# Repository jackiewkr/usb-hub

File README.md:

# 5.25" drive bay USB hub

## Why?
My PC case lacks front IO, due to it being from the early 90s. As such, all the USB headers
are located at the back of the motherboard. The pin headers for front IO on my motherboard
are unused, so this project should rectify that.

## What?
The aim is to create a 4-port USB hub, able to be mounted within a 5.25" PC drive bay.
More (semi-)detailed specifications below:
- Have 4 downstream USB 2.0 high-speed capable ports
- Be powered by standard Molex connector (aka 4-pin peripheral power connectors)
- Include current sensing on a port-by-port basis (don't kill all ports if only one overcurrents)
- Need no configuration from the user (work automatically once connected)
- Not to kill my motherboard or power supply

## Current Status
- Schematic designed fully [done]
- Initial PCB layout designed [working]
- First boards manufactured & tested [not yet]
- Revised boards [not yet]
- Outer case designed & printed [not yet]

## Schematic Details
The design is based of the Microchip USB2504, a 4-port USB 2.0 hub controller IC. 
The schematic largely follows the design of the evaluation board schematic, with
changes to limit certain functionality (no LEDs, EVB uses ganged current sensing, etc.)

Note that this schematic uses the TPS2560 for current sensing. The OUT1, OUT2 pins
are mis-assigned in the KiCad library as Output instead of Power Output. Please ignore
any errors generated in the DRC due to this.

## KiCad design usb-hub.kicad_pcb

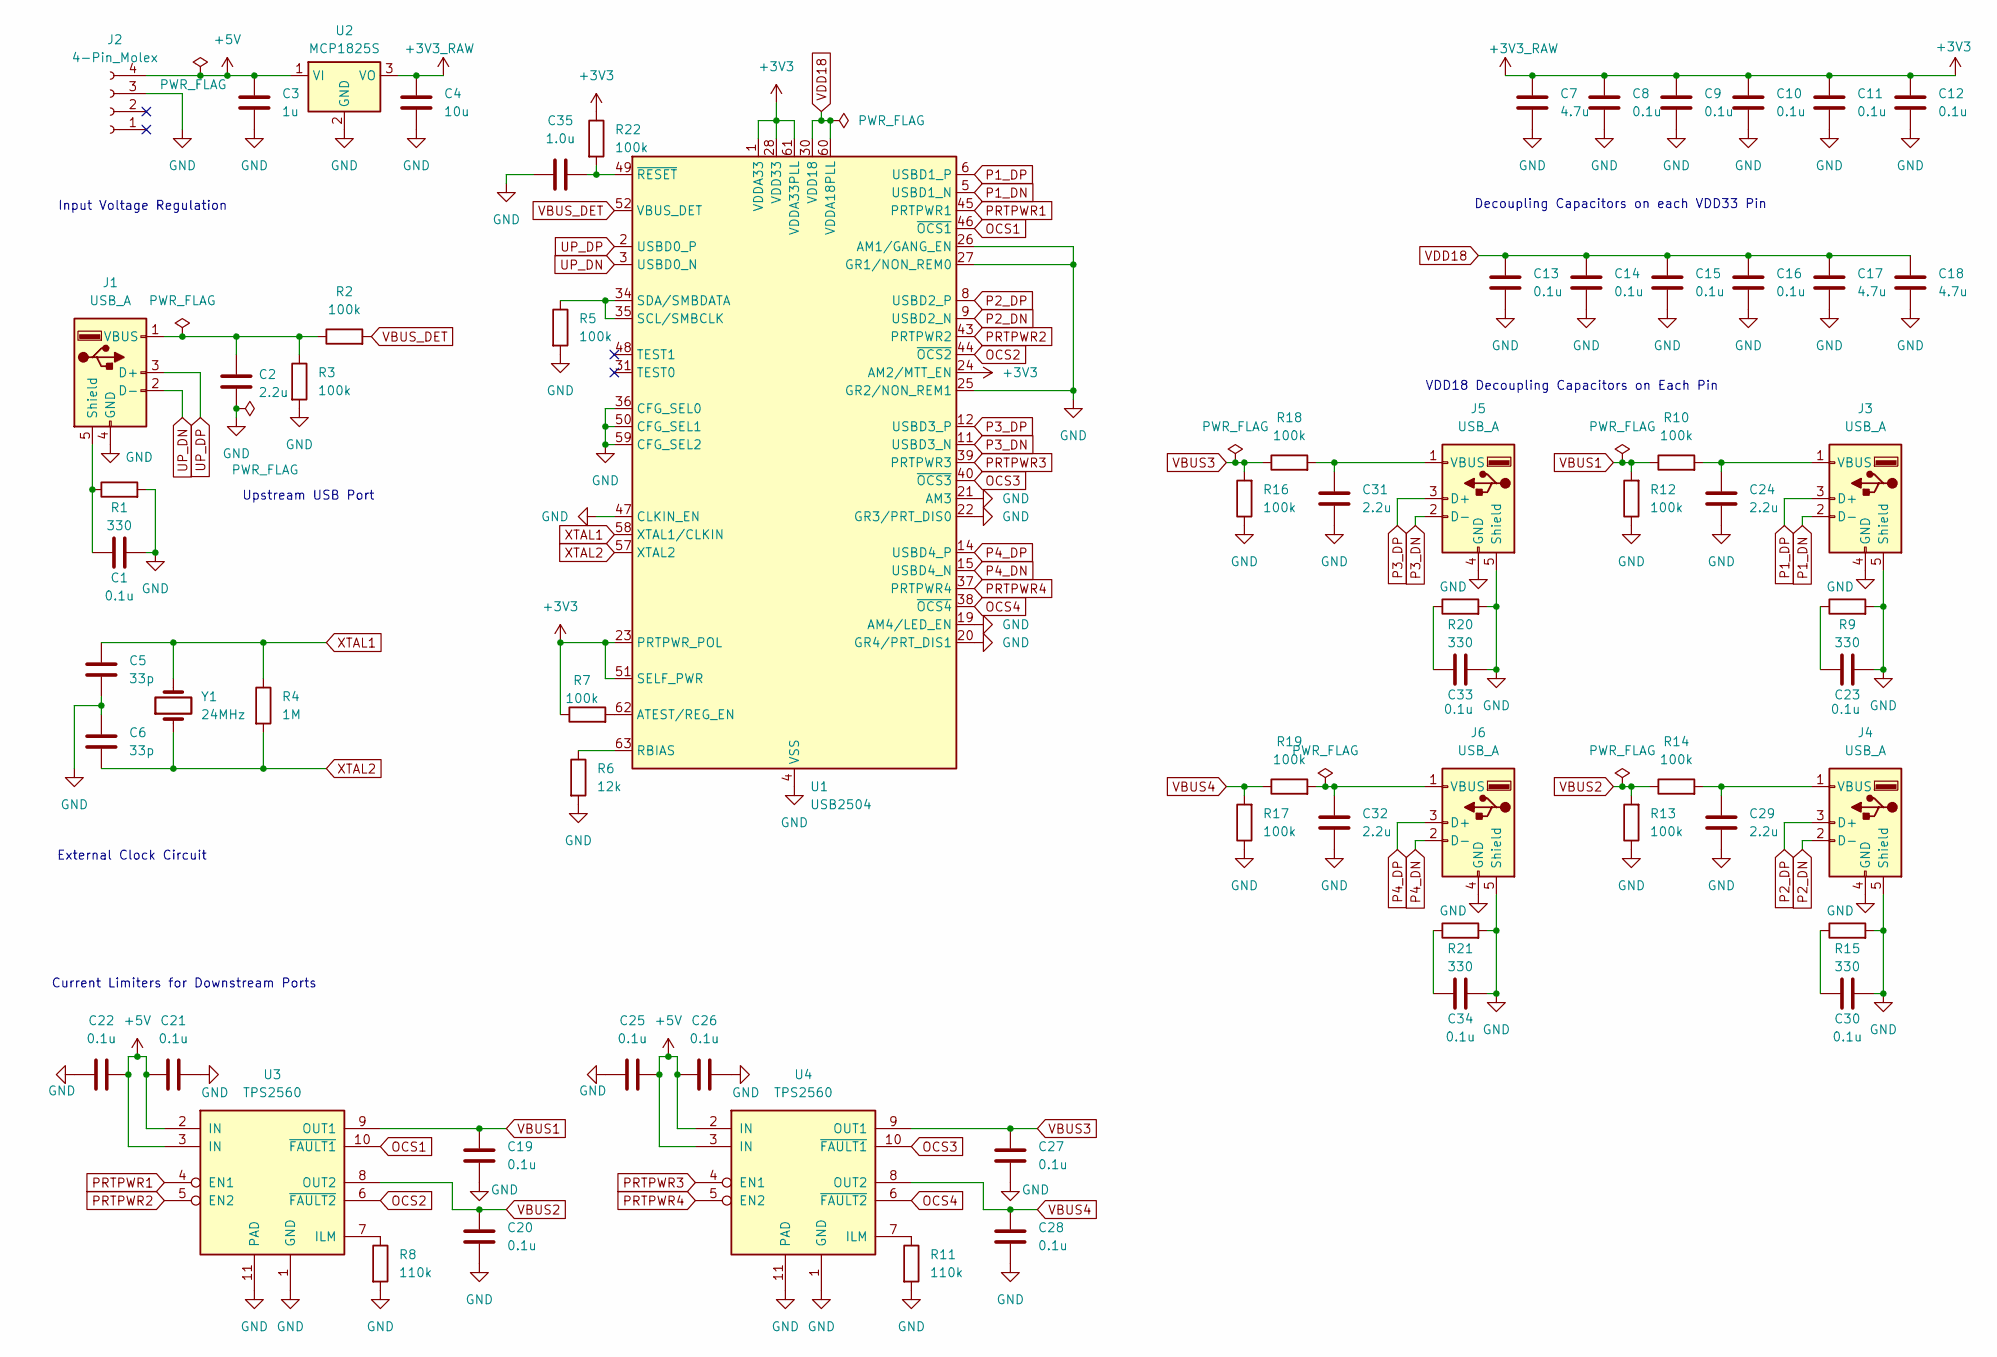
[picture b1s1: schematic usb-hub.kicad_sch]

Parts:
C1, C8, C9, C10, C11, C12, C13, C14, C15, C16, C19, C20, C21, C22, C23, C25, C26, C27, C28, C30, C33, C34: 0.1u; R_0805_2012Metric_Pad1.20x1.40mm_HandSolder
C2, C24, C29, C31, C32: 2.2u; R_0805_2012Metric_Pad1.20x1.40mm_HandSolder
C3: 1u; R_0805_2012Metric_Pad1.20x1.40mm_HandSolder
C4: 10u; R_0805_2012Metric_Pad1.20x1.40mm_HandSolder
C5, C6: 33p; R_0805_2012Metric_Pad1.20x1.40mm_HandSolder
C7, C17, C18: 4.7u; R_0805_2012Metric_Pad1.20x1.40mm_HandSolder
C35: 1.0u; R_0805_2012Metric_Pad1.20x1.40mm_HandSolder
J1, J3, J4, J5, J6: USB_A; USB_A_Receptacle_GCT_USB1046
J2: 4-Pin_Molex; SolderWire-1sqmm_1x04_P5.4mm_D1.4mm_OD2.7mm
R1, R9, R15, R20, R21: 330; R_0805_2012Metric_Pad1.20x1.40mm_HandSolder
R2, R3, R5, R7, R10, R12, R13, R14, R16, R17, R18, R19, R22: 100k; R_0805_2012Metric_Pad1.20x1.40mm_HandSolder
R4: 1M; R_0805_2012Metric_Pad1.20x1.40mm_HandSolder
R6: 12k; R_0805_2012Metric_Pad1.20x1.40mm_HandSolder
R8, R11: 110k; R_0805_2012Metric_Pad1.20x1.40mm_HandSolder
U1: USB2504; LQFP-64_10x10mm_P0.5mm
U2: MCP1825S; SOT-223
U3, U4: TPS2560; VSON-10-1EP_3x3mm_P0.5mm_EP1.65x2.4mm_ThermalVias
Y1: 24MHz; Crystal_SMD_2016-4Pin_2.0x1.6mm

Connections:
+3V3: C4.1, C7.1, C8.1, C9.1, C10.1, C11.1, C12.1, R7.1, R22.1, U1.1 (VDDA33), U1.7 (VDDA33), U1.13 (VDDA33), U1.23 (PRTPWR_POL), U1.24 (AM2/MTT_EN), U1.28 (VDD33), U1.51 (SELF_PWR), U1.61 (VDDA33PLL), U2.3 (VO)
+5V: C3.1, C21.1, C22.2, C25.2, C26.1, J2.4, U2.1 (VI), U3.2 (IN), U3.3 (IN), U4.2 (IN), U4.3 (IN)
GND: C1.2, C2.1, C3.2, C4.2, C5.2, C6.1, C7.2, C8.2, C9.2, C10.2, C11.2, C12.2, C13.2, C14.2, C15.2, C16.2, C17.2, C18.2, C19.2, C20.2, C21.2, C22.1, C23.2, C24.2, C25.1, C26.2, C27.2, C28.2, C29.2, C30.2, C31.2, C32.2, C33.2, C34.2, C35.1, J1.4 (GND), J2.3, J3.4 (GND), J3.5 (Shield), J4.4 (GND), J4.5 (Shield), J5.4 (GND), J5.5 (Shield), J6.4 (GND), J6.5 (Shield), R1.2, R3.2, R5.2, R6.2, R8.2, R9.2, R11.2, R12.1, R13.1, R15.2, R16.1, R17.1, R20.2, R21.2, U1.4 (VSS), U1.10 (VSS), U1.16 (VSS), U1.19 (AM4/LED_EN), U1.20 (GR4/PRT_DIS1), U1.21 (AM3), U1.22 (GR3/PRT_DIS0), U1.25 (GR2/NON_REM1), U1.26 (AM1/GANG_EN), U1.27 (GR1/NON_REM0), U1.29 (VSS), U1.36 (CFG_SEL0), U1.41 (VSS), U1.47 (CLKIN_EN), U1.50 (CFG_SEL1), U1.53 (VSS), U1.55 (VSS), U1.59 (CFG_SEL2), U1.64 (VSS), U2.2 (GND), U3.1 (GND), U3.11 (PAD), U4.1 (GND), U4.11 (PAD)
unnamed: C23.1, R9.1
unnamed: C30.1, R15.1
unnamed: C33.1, R20.1
unnamed: C34.1, R21.1
unnamed: C1.1, J1.5 (Shield), R1.1
unnamed: C2.2, J1.1 (VBUS), R2.1, R3.1
unnamed: C24.1, J3.1 (VBUS), R10.2
unnamed: C29.1, J4.1 (VBUS), R14.2
unnamed: C31.1, J5.1 (VBUS), R18.2
unnamed: C32.1, J6.1 (VBUS), R19.2
unnamed: R7.2, U1.62 (ATEST/REG_EN)
unnamed: R6.1, U1.63 (RBIAS)
unnamed: R5.1, U1.34 (SDA/SMBDATA), U1.35 (SCL/SMBCLK)
unnamed: C35.2, R22.2, U1.49 (~RESET)
unnamed: R8.1, U3.7 (ILM)
unnamed: R11.1, U4.7 (ILM)
OCS1: U1.46 (~OCS1), U3.10 (~FAULT1)
OCS2: U1.44 (~OCS2), U3.6 (~FAULT2)
OCS3: U1.40 (~OCS3), U4.10 (~FAULT1)
OCS4: U1.38 (~OCS4), U4.6 (~FAULT2)
P1_DN: J3.2 (D-), U1.5 (USBD1_N)
P1_DP: J3.3 (D+), U1.6 (USBD1_P)
P2_DN: J4.2 (D-), U1.9 (USBD2_N)
P2_DP: J4.3 (D+), U1.8 (USBD2_P)
P3_DN: J5.2 (D-), U1.11 (USBD3_N)
P3_DP: J5.3 (D+), U1.12 (USBD3_P)
P4_DN: J6.2 (D-), U1.15 (USBD4_N)
P4_DP: J6.3 (D+), U1.14 (USBD4_P)
PRTPWR1: U1.45 (PRTPWR1), U3.4 (EN1)
PRTPWR2: U1.43 (PRTPWR2), U3.5 (EN2)
PRTPWR3: U1.39 (PRTPWR3), U4.4 (EN1)
PRTPWR4: U1.37 (PRTPWR4), U4.5 (EN2)
UP_DN: J1.2 (D-), U1.3 (USBD0_N)
UP_DP: J1.3 (D+), U1.2 (USBD0_P)
VBUS1: C19.1, R10.1, R12.2, U3.9 (OUT1)
VBUS2: C20.1, R13.2, R14.1, U3.8 (OUT2)
VBUS3: C27.1, R16.2, R18.1, U4.9 (OUT1)
VBUS4: C28.1, R17.2, R19.1, U4.8 (OUT2)
VBUS_DET: R2.2, U1.52 (VBUS_DET)
VDD18: C13.1, C14.1, C15.1, C16.1, C17.1, C18.1, U1.30 (VDD18), U1.42 (VDD18), U1.54 (VDD18), U1.60 (VDDA18PLL)
XTAL1: C5.1, R4.1, U1.58 (XTAL1/CLKIN), Y1.2
XTAL2: C6.2, R4.2, U1.57 (XTAL2), Y1.1

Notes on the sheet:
Input Voltage Regulation
Decoupling Capacitors on each VDD33 Pin
Upstream USB Port
External Clock Circuit
Current Limiters for Downstream Ports
VDD18 Decoupling Capacitors on Each Pin

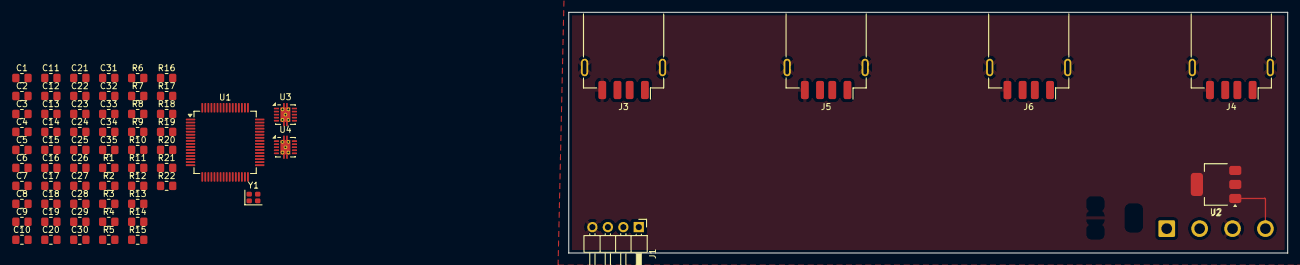
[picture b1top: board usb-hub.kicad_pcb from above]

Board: 2 copper layers, 118.0 x 39.5 mm, 68 parts (0 on the bottom side), 45 nets.

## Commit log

2026-02-25 Added initial schematic design
    Initial schematic design and basic positioning of USB headers on PCB board.
2026-02-25 Added schematic printout
